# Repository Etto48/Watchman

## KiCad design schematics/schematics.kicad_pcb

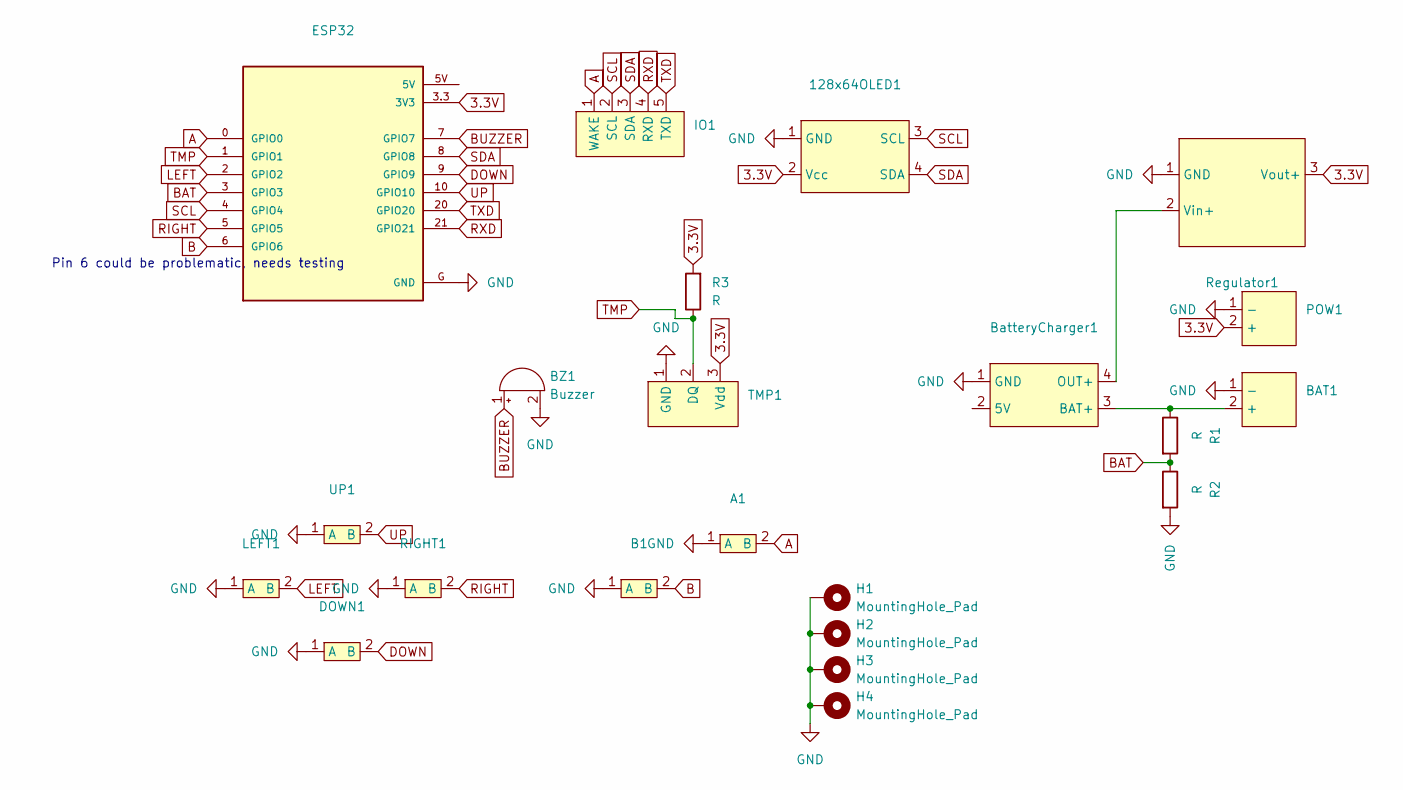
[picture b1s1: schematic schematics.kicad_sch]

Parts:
128x64OLED1: 128x64OLED
A1: SW_PUSH_6mm
B1: SW_PUSH_6mm
BAT1: PowerHeader BACKSIDE
BZ1: Buzzer; MagneticBuzzer_StarMicronics_QMX
BatteryCharger1: TP4056-18650
DOWN1: SW_PUSH_6mm
ESP32: MODULE_ESP32-C3_SUPERMINI_TH
H1, H2, H3, H4: MountingHole_Pad; MountingHole_2.2mm_M2_DIN965_Pad_TopBottom
IO1: IOPins
LEFT1: SW_PUSH_6mm
POW1: PowerHeader
R1, R2, R3: R; R_Axial_DIN0207_L6.3mm_D2.5mm_P10.16mm_Horizontal
RIGHT1: SW_PUSH_6mm
Regulator1: BuckBoost3.3V_0.85A
TMP1: TMPSensor
UP1: SW_PUSH_6mm

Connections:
3.3V: 128x64OLED1.2 (Vcc), ESP32.3.3 (3V3), POW1.2 (+), R3.2, Regulator1.3 (Vout+), TMP1.3 (Vdd)
A: A1.2 (B), ESP32.0 (GPIO0), IO1.1 (WAKE)
B: B1.2 (B), ESP32.6 (GPIO6)
BAT: ESP32.3 (GPIO3), R1.2, R2.1
BUZZER: BZ1.1 (+), ESP32.7 (GPIO7)
DOWN: DOWN1.2 (B), ESP32.9 (GPIO9)
GND: 128x64OLED1.1 (GND), A1.1 (A), B1.1 (A), BAT1.1 (-), BZ1.2 (-), BatteryCharger1.1 (GND), DOWN1.1 (A), ESP32.G (GND), H1.1, H2.1, H3.1, H4.1, LEFT1.1 (A), POW1.1 (-), R2.2, RIGHT1.1 (A), Regulator1.1 (GND), TMP1.1 (GND), UP1.1 (A)
LEFT: ESP32.2 (GPIO2), LEFT1.2 (B)
unnamed: BAT1.2 (+), BatteryCharger1.3 (BAT+), R1.1
unnamed: BatteryCharger1.4 (OUT+), Regulator1.2 (Vin+)
RIGHT: ESP32.5 (GPIO5), RIGHT1.2 (B)
RXD: ESP32.21 (GPIO21), IO1.4 (RXD)
SCL: 128x64OLED1.3 (SCL), ESP32.4 (GPIO4), IO1.2 (SCL)
SDA: 128x64OLED1.4 (SDA), ESP32.8 (GPIO8), IO1.3 (SDA)
TMP: ESP32.1 (GPIO1), R3.1, TMP1.2 (DQ)
TXD: ESP32.20 (GPIO20), IO1.5 (TXD)
UP: ESP32.10 (GPIO10), UP1.2 (B)

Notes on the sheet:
Pin 6 could be problematic, needs testing

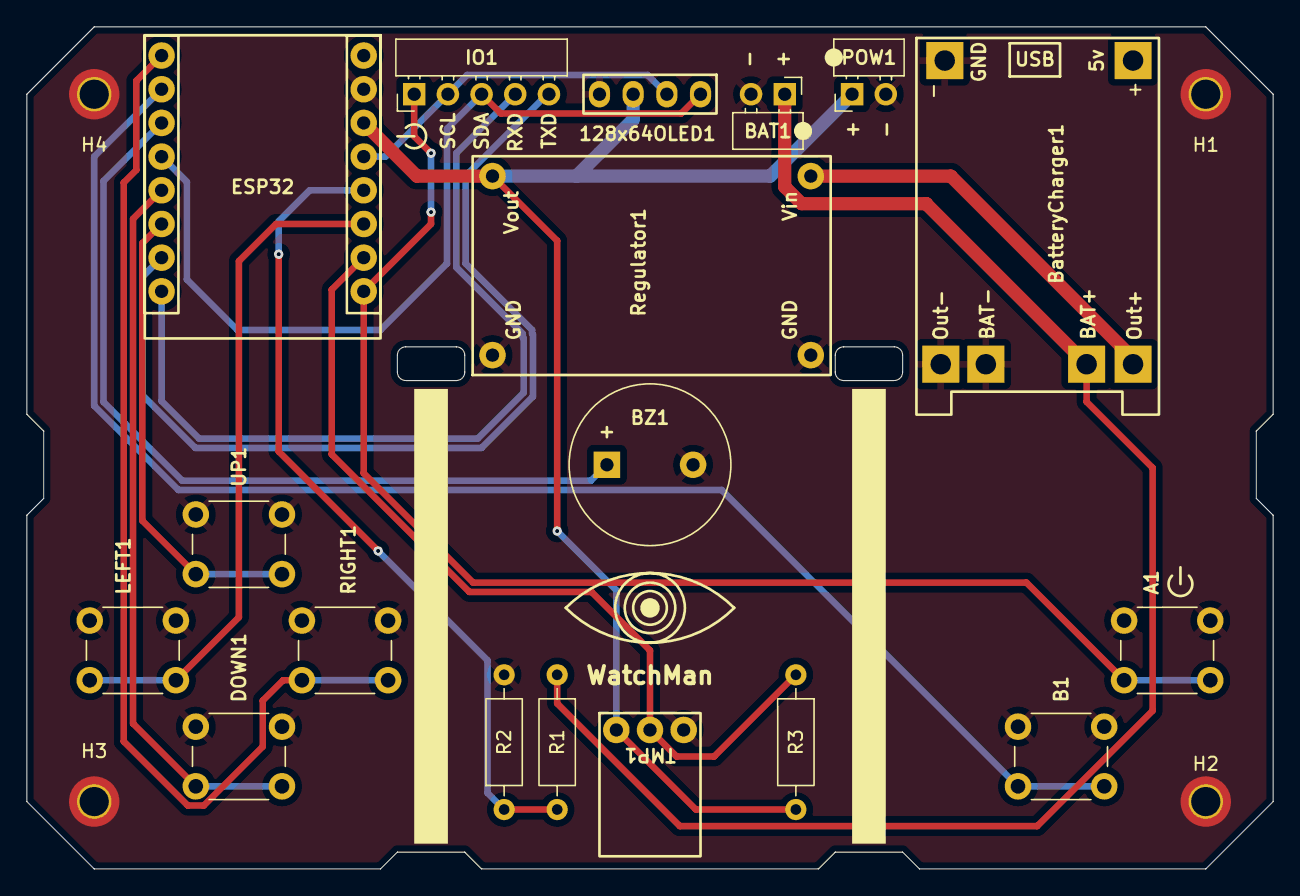
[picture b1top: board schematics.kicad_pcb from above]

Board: 2 copper layers, 94.0 x 63.5 mm, 23 parts (0 on the bottom side), 17 nets.

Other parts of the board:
Battery: Battery

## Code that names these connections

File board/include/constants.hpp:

#pragma once
#include <cstdint>

constexpr uint64_t SCREEN_WIDTH = 128; // OLED display width, in pixels
constexpr uint64_t SCREEN_HEIGHT = 64; // OLED display height, in pixels
constexpr uint8_t OLED_ADDR = 0x3C;
constexpr uint32_t MONITOR_SPEED = 115200;

constexpr uint8_t A_PIN = 0;
constexpr uint8_t B_PIN = 6;
constexpr uint8_t UP_PIN = 10;
constexpr uint8_t DOWN_PIN = 9;
constexpr uint8_t LEFT_PIN = 2;
constexpr uint8_t RIGHT_PIN = 5;

constexpr uint8_t TMP_PIN = 1;
constexpr uint8_t BAT_PIN = 3;
constexpr uint8_t BUZZER_PIN = 7;

constexpr uint8_t TXD_PIN = 20;
constexpr uint8_t RXD_PIN = 21;

constexpr uint8_t SDA_PIN = 8;
constexpr uint8_t SCL_PIN = 4;

constexpr uint8_t EVENT_QUEUE_SIZE = 16;
constexpr uint64_t DEBOUNCE_DELAY_US = 300000;
constexpr uint64_t REPEAT_DELAY_US = 500000;

constexpr uint64_t TIME_BEFORE_DEEPSLEEP_US = 60000000; // 1 minute of inactivity before going to deep sleep
constexpr uint64_t DEEPSLEEP_GRACE_PERIOD_US = 5000000; // 5 seconds grace period in deep sleep before sleeping
constexpr uint64_t UPDATE_STATUS_INTERVAL_MS = 1000; // Update status info every second

constexpr float BATTERY_MAX_VOLTAGE = 4.2f; // Maximum battery voltage
constexpr float BATTERY_MIN_VOLTAGE = 3.0f; // Minimum battery voltage
constexpr float BATTERY_R1 = 100e+3f; // Resistor R1 value in ohms
constexpr float BATTERY_R2 = 100e+3f;  // Resistor R2
constexpr float BATTERY_CHARGE_VOLTAGE = 4.5f; // Charging voltage
constexpr float BATTERY_DISCONNECTED_VOLTAGE = 1.0f; // Voltage indicating battery is disconnected

constexpr uint16_t MAX_ANALOG_READ = 4095; // 12-bit ADC
constexpr float ANALOG_REF_VOLTAGE = 3.3f; // Reference voltage for ADC

constexpr size_t DAYLIGHT_OFFSET_S = 3600; // Daylight saving time offset

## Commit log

2025-12-17 Update schematics. version with removable esp32
2025-12-21 Real code for the real version of the board
2025-12-21 removed bad arduino extension files
2025-12-21 better logging
2025-12-21 redesigned events with a real queue, made music interruptible again
2025-12-21 add sleep grace period
2025-12-21 add readme and license
2025-12-21 update real components + explode
2025-12-24 add more applications
2025-12-25 add wifi manager and virtual keyboard interface
2025-12-25 fix clock (workaround)
2025-12-26 add settings
2025-12-27 add metronome app
2025-12-28 add event debugger and more powerful events
2025-12-28 add key repeat event
2025-12-31 Add battery disconnected check and icon, fixed wifi bug (maybe) and made music playback stop more responsive
2026-01-05 add RTC manual setting, alarm icon and calendar app
2026-01-09 add battery app and better icons
